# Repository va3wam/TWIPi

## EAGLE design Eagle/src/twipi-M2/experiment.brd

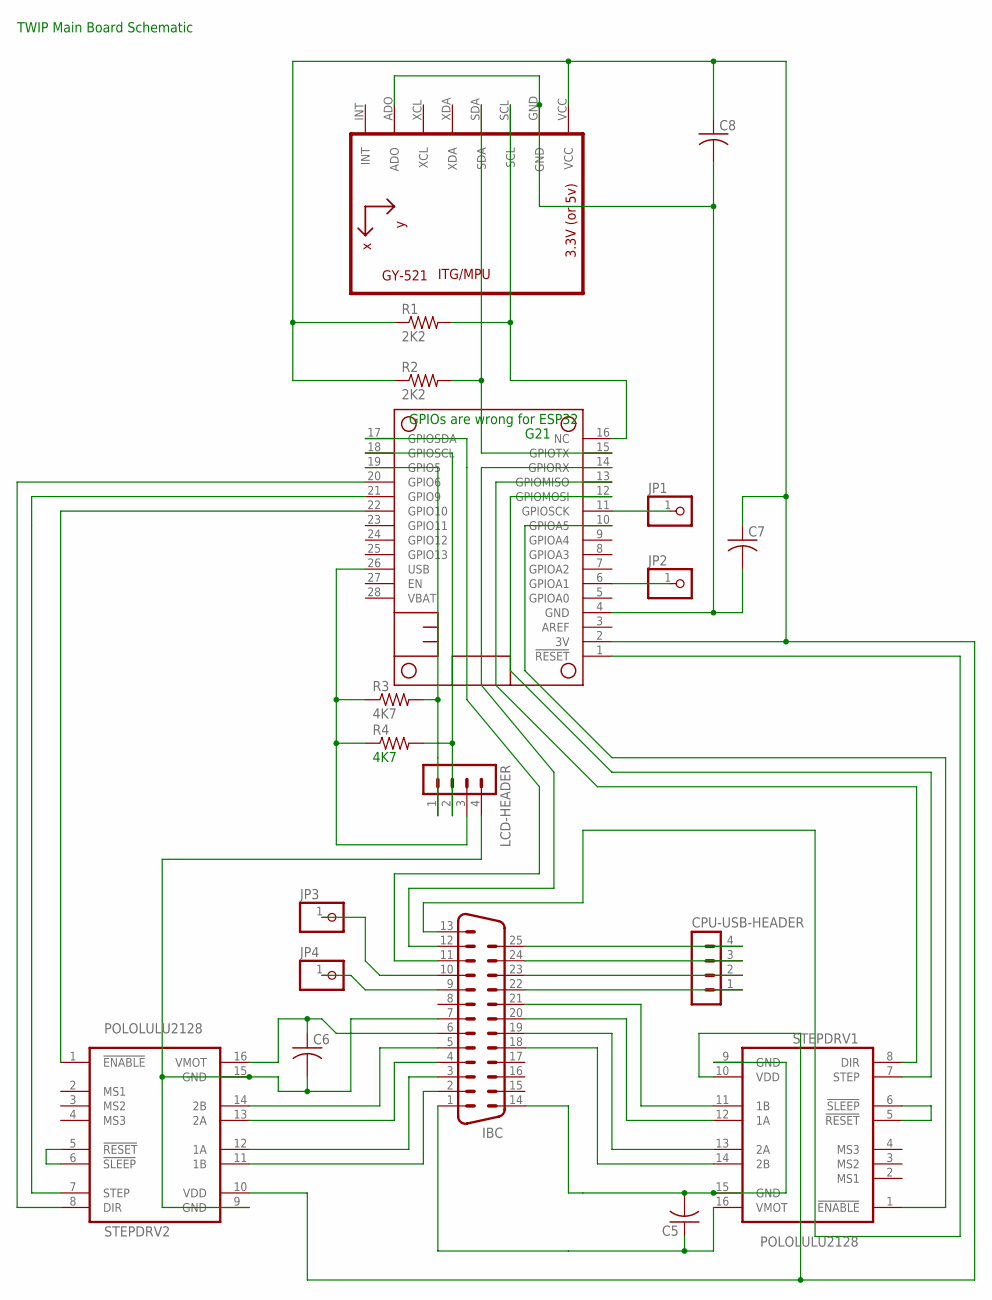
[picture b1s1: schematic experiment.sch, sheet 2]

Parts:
C5, C6, C7, C8: C-US050-024X044; C050-024X044
CPU-USB-HEADER: MA04-1
IBC: M25VP
JP1, JP2, JP3, JP4: PINHD-1X1; 1X01
LCD-HEADER: MA04-1
MS2: FEATHERWING_NOHOLES
R1, R2: 2K2; 0309/12
R3, R4: 4K7; 0309/12
STEPDRV1, STEPDRV2: POLOLULU2128
U1: GY-521MPU6050; GY-521

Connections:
3V: C7.1, C8.1, MS2.2 (3V), R1.1, R2.1, STEPDRV1.10 (VDD), STEPDRV2.10 (VDD), U1.VCC
unnamed: C7.2, C8.2, MS2.4 (GND), U1.ADO, U1.GND
unnamed: IBC.18, STEPDRV1.14 (2B)
unnamed: IBC.19, STEPDRV1.13 (2A)
unnamed: MS2.12 (GPIOMOSI), STEPDRV1.7 (STEP)
unnamed: IBC.20, STEPDRV1.12 (1A)
unnamed: IBC.21, STEPDRV1.11 (1B)
unnamed: IBC.2, STEPDRV2.11 (1B)
unnamed: IBC.3, STEPDRV2.12 (1A)
unnamed: IBC.4, STEPDRV2.13 (2A)
unnamed: LCD-HEADER.1, MS2.19 (GPIO5), R3.2
unnamed: IBC.5, STEPDRV2.14 (2B)
unnamed: CPU-USB-HEADER.4, IBC.25
unnamed: CPU-USB-HEADER.3, IBC.24
unnamed: MS2.13 (GPIOMISO), STEPDRV1.8 (DIR)
unnamed: IBC.13, MS2.1 (!RESET)
unnamed: MS2.16 (NC), R1.2, U1.SCL
unnamed: CPU-USB-HEADER.2, IBC.23
unnamed: IBC.12, MS2.14 (GPIORX)
unnamed: C5.2, IBC.14, STEPDRV1.9 (GND), STEPDRV1.15 (GND)
unnamed: C6.1, IBC.6, STEPDRV2.16 (VMOT)
unnamed: C5.1, IBC.1, STEPDRV1.16 (VMOT)
unnamed: STEPDRV1.5 (!RESET), STEPDRV1.6 (!SLEEP)
unnamed: STEPDRV2.5 (!RESET), STEPDRV2.6 (!SLEEP)
unnamed: MS2.15 (GPIOTX), R2.2, U1.SDA
unnamed: MS2.20 (GPIO6), STEPDRV2.8 (DIR)
unnamed: IBC.11, MS2.17 (GPIOSDA)
unnamed: MS2.21 (GPIO9), STEPDRV2.7 (STEP)
unnamed: CPU-USB-HEADER.1, IBC.22
unnamed: MS2.10 (GPIOA5), STEPDRV1.1 (!ENABLE)
unnamed: JP1.1, MS2.11 (GPIOSCK)
unnamed: C6.2, IBC.7, LCD-HEADER.4, STEPDRV2.9 (GND), STEPDRV2.15 (GND)
unnamed: MS2.22 (GPIO10), STEPDRV2.1 (!ENABLE)
unnamed: LCD-HEADER.2, MS2.18 (GPIOSCL), R4.2
unnamed: JP2.1, MS2.6 (GPIOA1)
unnamed: IBC.10, JP3.1
unnamed: IBC.9, JP4.1
USB: LCD-HEADER.3, MS2.26 (USB), R3.1, R4.1

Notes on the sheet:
GPIOs are wrong for ESP32
G21
TWIP Main Board Schematic

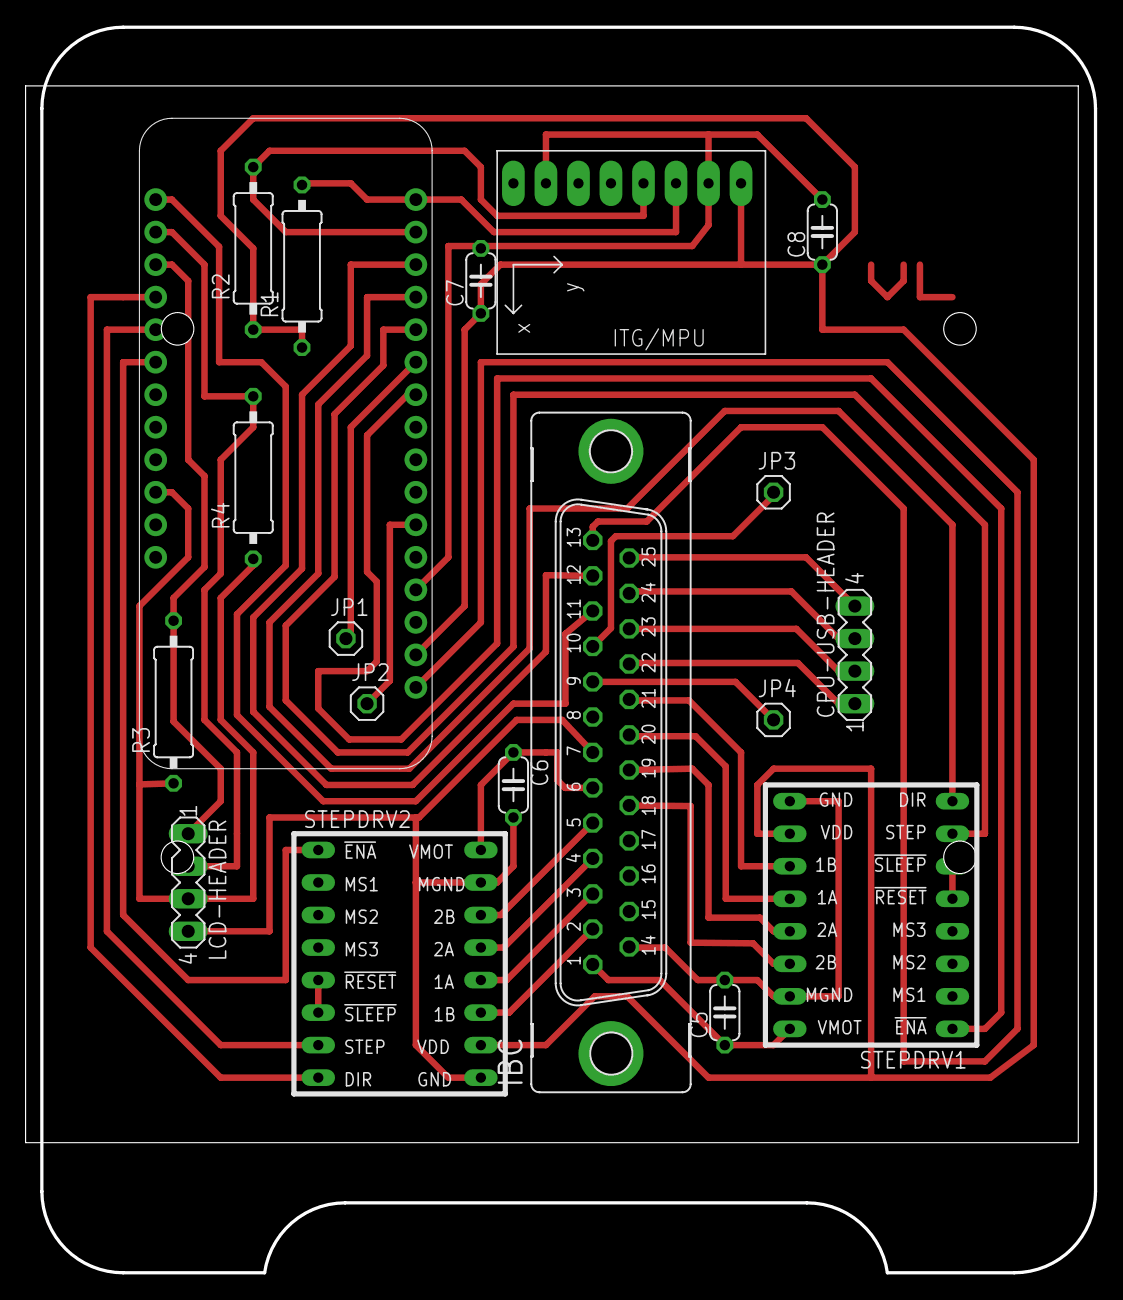
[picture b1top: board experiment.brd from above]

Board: 2 copper layers, 83.6 x 97.3 mm, 19 parts (0 on the bottom side), 38 nets.

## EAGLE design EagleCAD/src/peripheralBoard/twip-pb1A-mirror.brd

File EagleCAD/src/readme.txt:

This is where the Schematic (SCH) and Layout (BRD) files for EagleCAD PCBs go

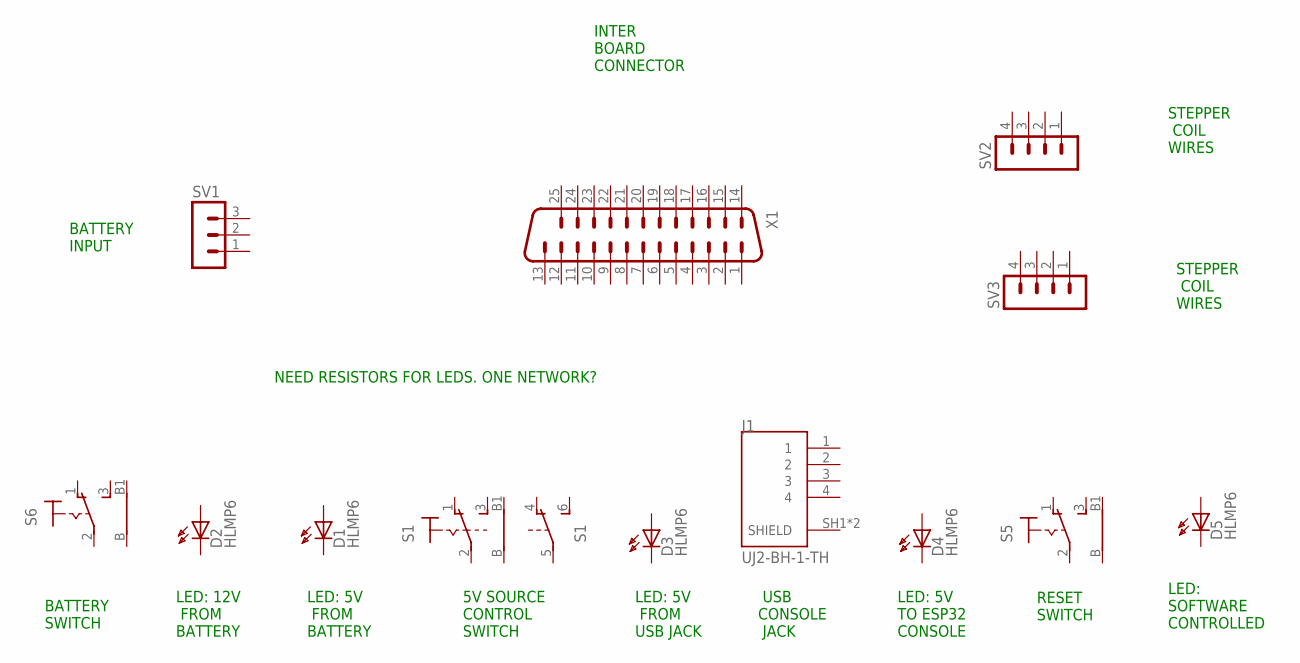
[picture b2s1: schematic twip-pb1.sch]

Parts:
D1, D2, D3, D4, D5: HLMP6
J1: UJ2-BH-1-TH; CUI_UJ2-BH-1-TH
S1: 9070-2W
S5, S6: 9070-1W
SV1: MA03-1
SV2, SV3: MA04-1
X1: M25VP

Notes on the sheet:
BATTERY SWITCH
LED: 5V FROM BATTERY
LED: 12V FROM BATTERY
LED: 5V TO ESP32 CONSOLE
LED: SOFTWARE CONTROLLED
RESET SWITCH
5V SOURCE CONTROL SWITCH
LED: 5V FROM USB JACK
USB CONSOLE JACK
BATTERY INPUT
STEPPER COIL WIRES
INTER BOARD CONNECTOR
NEED RESISTORS FOR LEDS. ONE NETWORK?

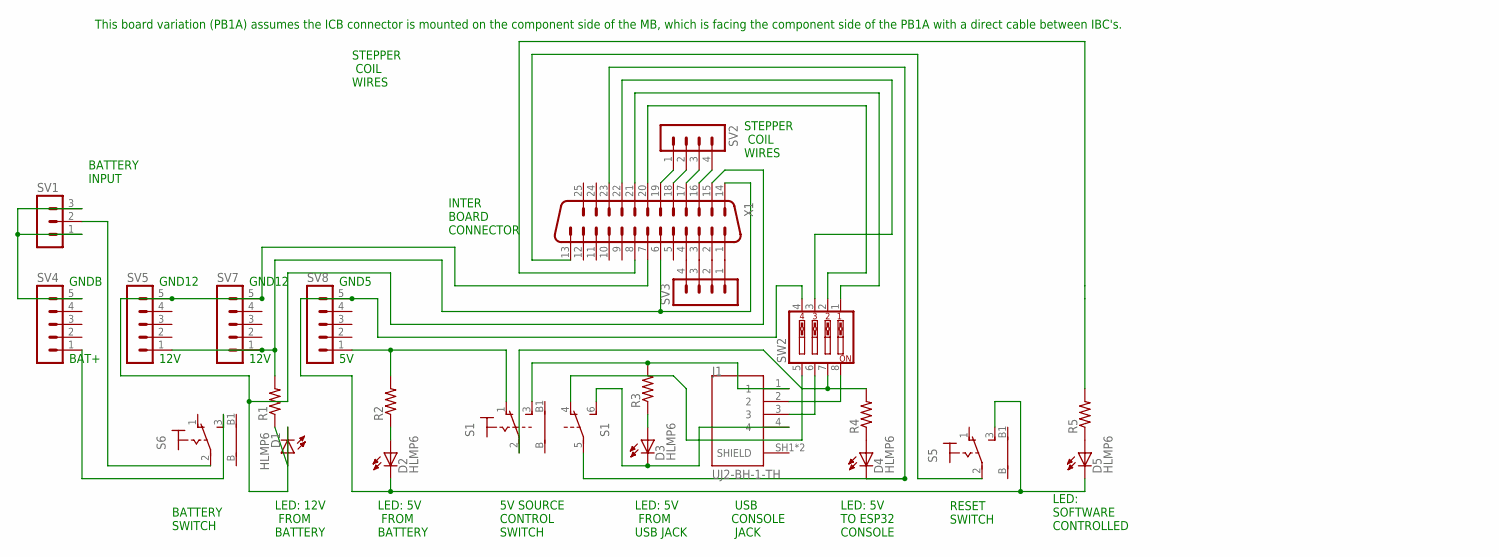
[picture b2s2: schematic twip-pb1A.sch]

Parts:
D1, D2, D3, D4, D5: HLMP6
J1: UJ2-BH-1-TH; CUI_UJ2-BH-1-TH
R1, R2, R3, R4, R5: R-US_0207/5V; 0207/5V
S1: 9070-2W
S5, S6: 9070-1W
SV1: MA03-1
SV2, SV3: MA04-1
SV4, SV5, SV7, SV8: MA05-1
SW2: SW_DIP-4; EDG-04
X1: M25VP

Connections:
unnamed: D1.A, R1.1
unnamed: D2.A, R2.1
unnamed: D3.A, R3.1
unnamed: D4.A, R4.1
unnamed: D5.A, R5.1
unnamed: SV1.1, SV1.3, SV4.5
unnamed: S6.2, SV1.2
unnamed: R1.2, SV5.1, SV7.1, X1.6, X1.14
unnamed: J1.1, R3.2, S1.3 (S)
unnamed: S6.3 (S), SV4.1
unnamed: SV2.1, X1.19
unnamed: R2.2, S1.1 (O), SV8.1
unnamed: J1.2, SW2.8
unnamed: SV3.4, X1.4
unnamed: SV3.3, X1.3
unnamed: SV3.2, X1.2
unnamed: SV3.1, X1.1
unnamed: SV2.2, X1.18
unnamed: SV2.3, X1.17
unnamed: SV2.4, X1.16
unnamed: R5.2, X1.8
unnamed: R4.2, S1.2, SW2.7
unnamed: D3.K, J1.4, S1.6 (S)
unnamed: SW2.1, X1.21
unnamed: SW2.3, X1.22
unnamed: SW2.2, X1.20
unnamed: D4.K, S1.5, X1.23
unnamed: S5.2, X1.13
unnamed: D1.K, SV5.5, SV7.5, X1.7, X1.15
unnamed: S1.4 (O), SW2.5
unnamed: D2.K, D5.K, S5.3 (S), SV8.5, SW2.4
unnamed: J1.3, SW2.6

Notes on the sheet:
BATTERY SWITCH
LED: 5V FROM BATTERY
LED: 12V FROM BATTERY
LED: 5V TO ESP32 CONSOLE
LED: SOFTWARE CONTROLLED
RESET SWITCH
5V SOURCE CONTROL SWITCH
LED: 5V FROM USB JACK
USB CONSOLE JACK
BATTERY INPUT
STEPPER COIL WIRES
INTER BOARD CONNECTOR
This board variation (PB1A) assumes the ICB connector is mounted on the component side of the MB, which is facing the component side of the PB1A with a direct cable between IBC's.
12V
BAT+
GNDB
GND12
GND5

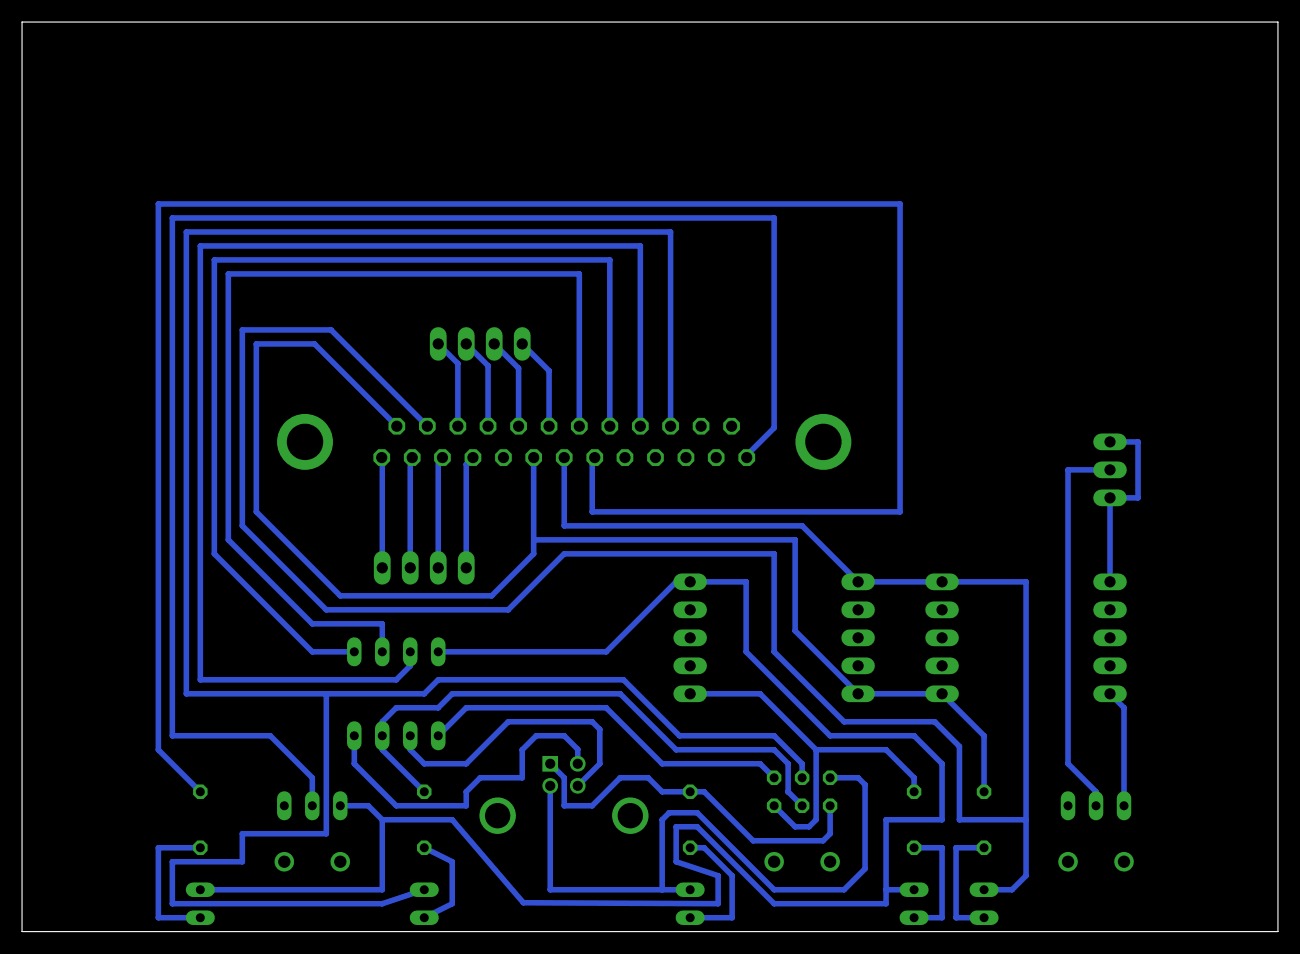
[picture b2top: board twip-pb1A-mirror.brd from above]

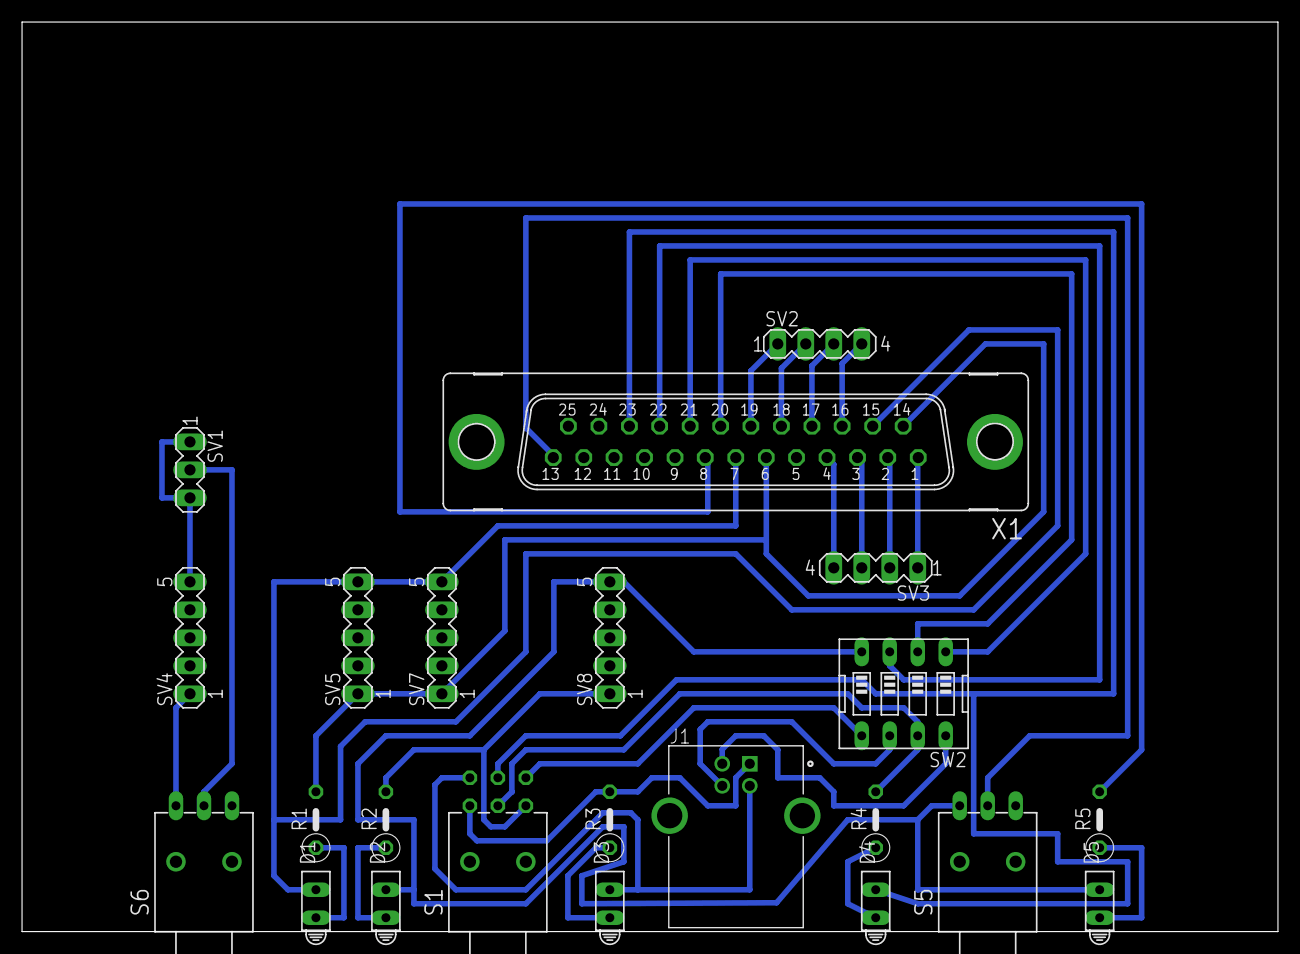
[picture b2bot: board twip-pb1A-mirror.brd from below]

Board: 2 copper layers, 114.0 x 82.5 mm, 23 parts (23 on the bottom side), 32 nets.

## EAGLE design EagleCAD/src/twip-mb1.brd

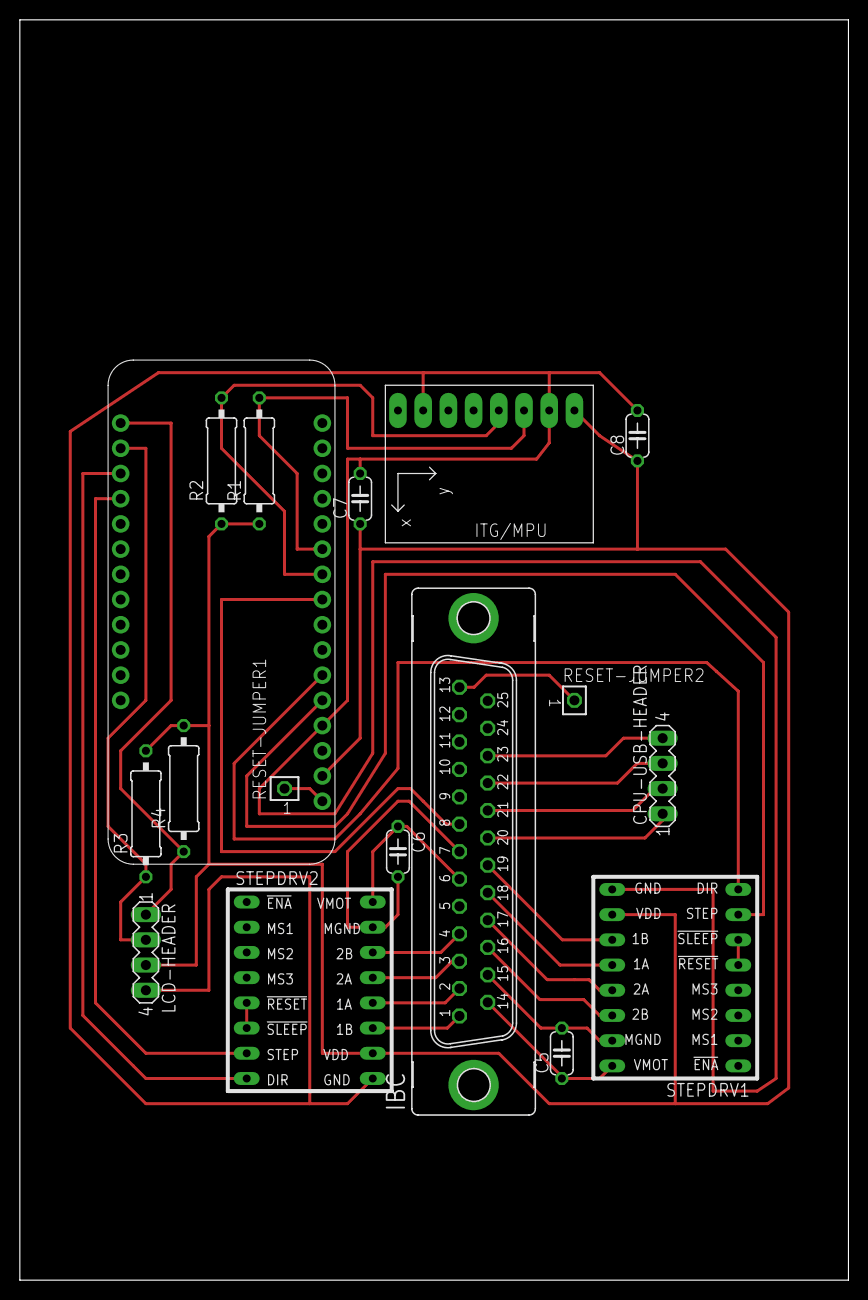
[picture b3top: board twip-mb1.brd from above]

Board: 2 copper layers, 83.5 x 127.0 mm, 17 parts (0 on the bottom side), 31 nets.

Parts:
C5, C6, C7, C8: C050-024X044
CPU-USB-HEADER: MA04-1
IBC: M25VP
LCD-HEADER: MA04-1
MS2: FEATHERWING_NOHOLES
R1, R2, R3, R4: 2K2; 0309/12
RESET-JUMPER1, RESET-JUMPER2: TSW-101-07-G-S; TSW-101-XX-G-S
STEPDRV1, STEPDRV2: POLOLULU2128
U1: GY-521MPU6050; GY-521

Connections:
3V: C7.1, C8.1, LCD-HEADER.3, MS2.2, R1.1, R2.1, R3.2, R4.2, STEPDRV1.10, STEPDRV2.10, U1.VCC
unnamed: IBC.13, RESET-JUMPER2.1
unnamed: C6.2, IBC.7, STEPDRV2.15
unnamed: IBC.16, STEPDRV1.14
unnamed: IBC.17, STEPDRV1.13
unnamed: MS2.5, STEPDRV1.7
unnamed: IBC.18, STEPDRV1.12
unnamed: IBC.19, STEPDRV1.11
unnamed: IBC.1, STEPDRV2.11
unnamed: IBC.2, STEPDRV2.12
unnamed: IBC.3, STEPDRV2.13
unnamed: LCD-HEADER.2, MS2.18, R3.1
unnamed: IBC.4, STEPDRV2.14
unnamed: CPU-USB-HEADER.4, IBC.23
unnamed: CPU-USB-HEADER.3, IBC.22
unnamed: MS2.6, STEPDRV1.8
unnamed: MS2.1, RESET-JUMPER1.1
unnamed: MS2.11, R1.2, U1.SCL
unnamed: CPU-USB-HEADER.2, IBC.21
unnamed: LCD-HEADER.1, MS2.17, R4.1
unnamed: C5.2, IBC.15, STEPDRV1.15
unnamed: C6.1, IBC.6, STEPDRV2.16
unnamed: C5.1, IBC.14, STEPDRV1.16
unnamed: STEPDRV1.5, STEPDRV1.6
unnamed: STEPDRV2.5, STEPDRV2.6
unnamed: MS2.10, R2.2, U1.SDA
unnamed: MS2.19, STEPDRV2.8
unnamed: IBC.8, MS2.9
unnamed: MS2.20, STEPDRV2.7
unnamed: CPU-USB-HEADER.1, IBC.20
unnamed: C7.2, C8.2, LCD-HEADER.4, MS2.4, STEPDRV1.9, STEPDRV2.9, U1.ADO, U1.GND
